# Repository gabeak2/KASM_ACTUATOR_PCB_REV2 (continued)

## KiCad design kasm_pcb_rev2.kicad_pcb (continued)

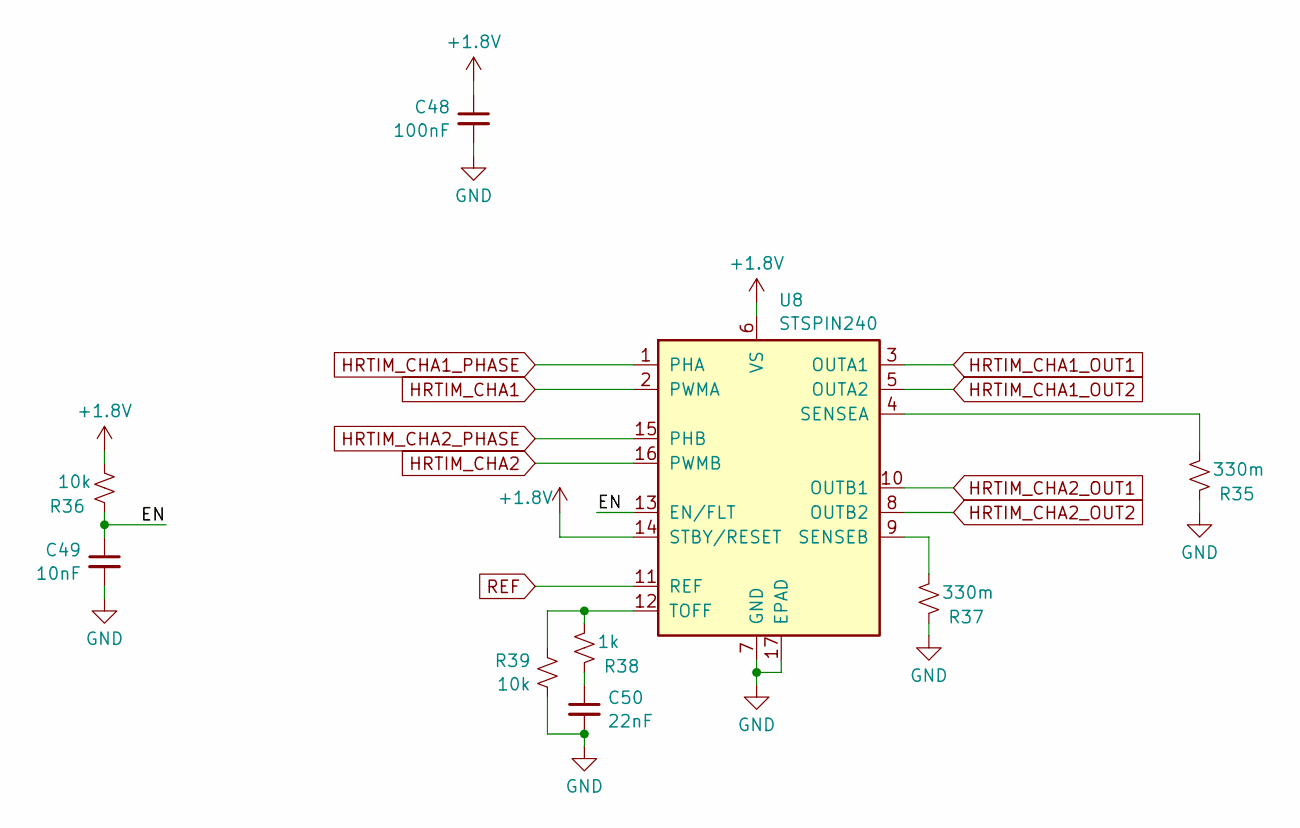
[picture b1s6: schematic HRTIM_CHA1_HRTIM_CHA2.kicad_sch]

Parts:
C48: 100nF; C_0402_1005Metric; LCSC C1525
C49: 10nF; C_0402_1005Metric; LCSC C15195
C50: 22nF; C_0402_1005Metric; LCSC C1532
R35, R37: 330m; R_0402_1005Metric; LCSC C332660
R36, R39: 10k; R_0402_1005Metric; LCSC C25744
R38: 1k; R_0402_1005Metric; LCSC C11702
U8: STSPIN240; VQFN-16-1EP_3x3mm_P0.5mm_EP1.8x1.8mm; LCSC C962258

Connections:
+1.8V: C48.1, R36.1, U8.6 (VS), U8.14 (STBY/RESET); also elsewhere on the board
/Actuators/HRTIM_CHA1_HRTIM_CHA2/EN: C49.1, R36.2, U8.13 (EN/FLT)
GND: C48.2, C49.2, C50.2, R35.2, R37.2, R39.2, U8.7 (GND), U8.17 (EPAD); also elsewhere on the board
HRTIM_CHA1: U8.2 (PWMA); also elsewhere on the board
HRTIM_CHA1_OUT1: U8.3 (OUTA1); also elsewhere on the board
HRTIM_CHA1_OUT2: U8.5 (OUTA2); also elsewhere on the board
HRTIM_CHA1_PHASE: U8.1 (PHA); also elsewhere on the board
HRTIM_CHA2: U8.16 (PWMB); also elsewhere on the board
HRTIM_CHA2_OUT1: U8.10 (OUTB1); also elsewhere on the board
HRTIM_CHA2_OUT2: U8.8 (OUTB2); also elsewhere on the board
HRTIM_CHA2_PHASE: U8.15 (PHB); also elsewhere on the board
unnamed: C50.1, R38.2
unnamed: R35.1, U8.4 (SENSEA)
unnamed: R37.1, U8.9 (SENSEB)
unnamed: R38.1, R39.1, U8.12 (TOFF)
REF: U8.11 (REF); also elsewhere on the board

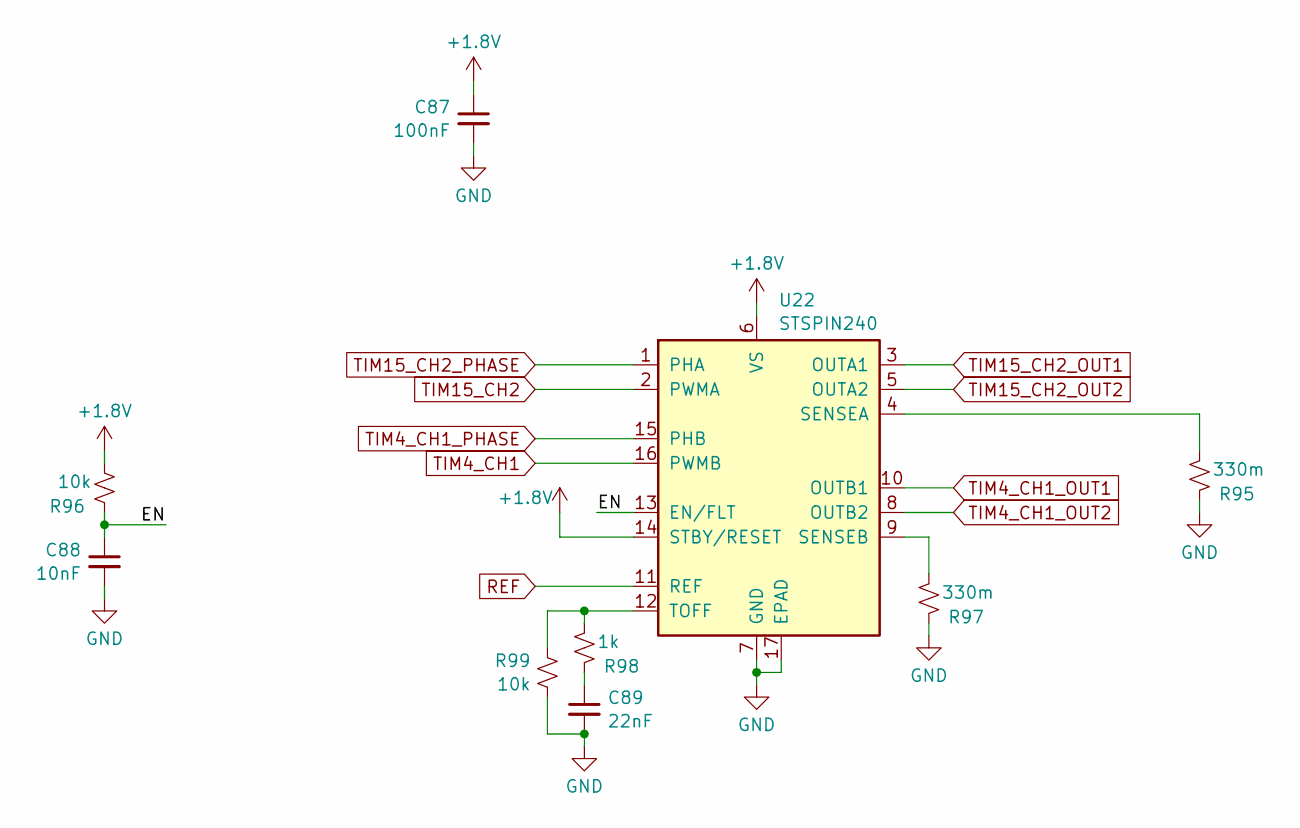
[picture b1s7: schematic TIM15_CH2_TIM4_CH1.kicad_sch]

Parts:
C87: 100nF; C_0402_1005Metric; LCSC C1525
C88: 10nF; C_0402_1005Metric; LCSC C15195
C89: 22nF; C_0402_1005Metric; LCSC C1532
R95, R97: 330m; R_0402_1005Metric; LCSC C332660
R96, R99: 10k; R_0402_1005Metric; LCSC C25744
R98: 1k; R_0402_1005Metric; LCSC C11702
U22: STSPIN240; VQFN-16-1EP_3x3mm_P0.5mm_EP1.8x1.8mm; LCSC C962258

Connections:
+1.8V: C87.1, R96.1, U22.6 (VS), U22.14 (STBY/RESET); also elsewhere on the board
/Actuators/TIM15_CH2_TIM4_CH1/EN: C88.1, R96.2, U22.13 (EN/FLT)
GND: C87.2, C88.2, C89.2, R95.2, R97.2, R99.2, U22.7 (GND), U22.17 (EPAD); also elsewhere on the board
unnamed: C89.1, R98.2
unnamed: R95.1, U22.4 (SENSEA)
unnamed: R97.1, U22.9 (SENSEB)
unnamed: R98.1, R99.1, U22.12 (TOFF)
REF: U22.11 (REF); also elsewhere on the board
TIM4_CH1: U22.16 (PWMB); also elsewhere on the board
TIM4_CH1_OUT1: U22.10 (OUTB1); also elsewhere on the board
TIM4_CH1_OUT2: U22.8 (OUTB2); also elsewhere on the board
TIM4_CH1_PHASE: U22.15 (PHB); also elsewhere on the board
TIM15_CH2: U22.2 (PWMA); also elsewhere on the board
TIM15_CH2_OUT1: U22.3 (OUTA1); also elsewhere on the board
TIM15_CH2_OUT2: U22.5 (OUTA2); also elsewhere on the board
TIM15_CH2_PHASE: U22.1 (PHA); also elsewhere on the board

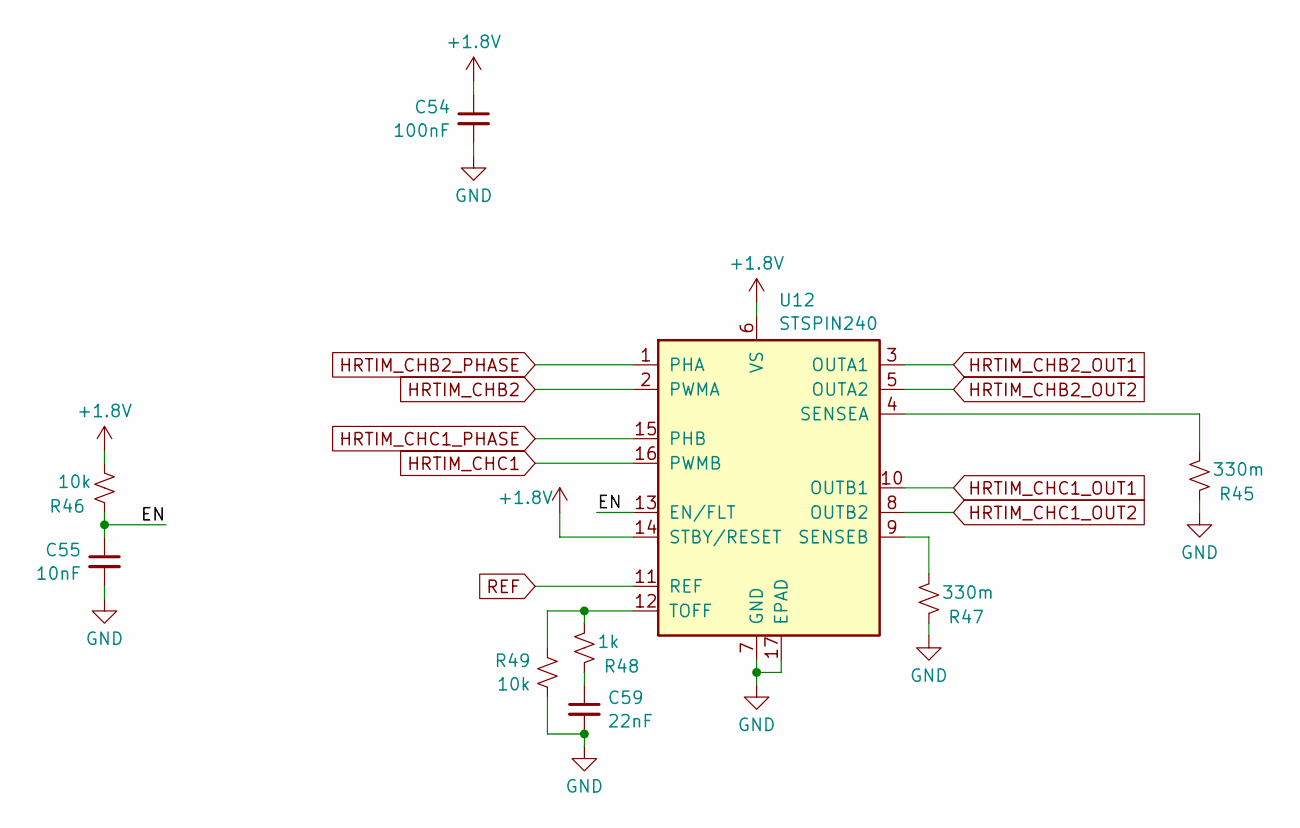
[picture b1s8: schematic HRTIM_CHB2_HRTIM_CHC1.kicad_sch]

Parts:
C54: 100nF; C_0402_1005Metric; LCSC C1525
C55: 10nF; C_0402_1005Metric; LCSC C15195
C59: 22nF; C_0402_1005Metric; LCSC C1532
R45, R47: 330m; R_0402_1005Metric; LCSC C332660
R46, R49: 10k; R_0402_1005Metric; LCSC C25744
R48: 1k; R_0402_1005Metric; LCSC C11702
U12: STSPIN240; VQFN-16-1EP_3x3mm_P0.5mm_EP1.8x1.8mm; LCSC C962258

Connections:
+1.8V: C54.1, R46.1, U12.6 (VS), U12.14 (STBY/RESET); also elsewhere on the board
/Actuators/HRTIM_CHB2_HRTIM_CHC1/EN: C55.1, R46.2, U12.13 (EN/FLT)
GND: C54.2, C55.2, C59.2, R45.2, R47.2, R49.2, U12.7 (GND), U12.17 (EPAD); also elsewhere on the board
HRTIM_CHB2: U12.2 (PWMA); also elsewhere on the board
HRTIM_CHB2_OUT1: U12.3 (OUTA1); also elsewhere on the board
HRTIM_CHB2_OUT2: U12.5 (OUTA2); also elsewhere on the board
HRTIM_CHB2_PHASE: U12.1 (PHA); also elsewhere on the board
HRTIM_CHC1: U12.16 (PWMB); also elsewhere on the board
HRTIM_CHC1_OUT1: U12.10 (OUTB1); also elsewhere on the board
HRTIM_CHC1_OUT2: U12.8 (OUTB2); also elsewhere on the board
HRTIM_CHC1_PHASE: U12.15 (PHB); also elsewhere on the board
unnamed: C59.1, R48.2
unnamed: R45.1, U12.4 (SENSEA)
unnamed: R47.1, U12.9 (SENSEB)
unnamed: R48.1, R49.1, U12.12 (TOFF)
REF: U12.11 (REF); also elsewhere on the board

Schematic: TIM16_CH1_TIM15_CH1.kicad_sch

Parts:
C78: 100nF; C_0402_1005Metric; LCSC C1525
C79: 10nF; C_0402_1005Metric; LCSC C15195
C80: 22nF; C_0402_1005Metric; LCSC C1532
R80, R82: 330m; R_0402_1005Metric; LCSC C332660
R81, R84: 10k; R_0402_1005Metric; LCSC C25744
R83: 1k; R_0402_1005Metric; LCSC C11702
U19: STSPIN240; VQFN-16-1EP_3x3mm_P0.5mm_EP1.8x1.8mm; LCSC C962258

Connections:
+1.8V: C78.1, R81.1, U19.6 (VS), U19.14 (STBY/RESET); also elsewhere on the board
/Actuators/TIM16_CH1_TIM15_CH1/EN: C79.1, R81.2, U19.13 (EN/FLT)
GND: C78.2, C79.2, C80.2, R80.2, R82.2, R84.2, U19.7 (GND), U19.17 (EPAD); also elsewhere on the board
unnamed: C80.1, R83.2
unnamed: R80.1, U19.4 (SENSEA)
unnamed: R82.1, U19.9 (SENSEB)
unnamed: R83.1, R84.1, U19.12 (TOFF)
REF: U19.11 (REF); also elsewhere on the board
TIM15_CH1: U19.16 (PWMB); also elsewhere on the board
TIM15_CH1_OUT1: U19.10 (OUTB1); also elsewhere on the board
TIM15_CH1_OUT2: U19.8 (OUTB2); also elsewhere on the board
TIM15_CH1_PHASE: U19.15 (PHB); also elsewhere on the board
TIM16_CH1: U19.2 (PWMA); also elsewhere on the board
TIM16_CH1_OUT1: U19.3 (OUTA1); also elsewhere on the board
TIM16_CH1_OUT2: U19.5 (OUTA2); also elsewhere on the board
TIM16_CH1_PHASE: U19.1 (PHA); also elsewhere on the board

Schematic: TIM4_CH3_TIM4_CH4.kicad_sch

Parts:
C75: 100nF; C_0402_1005Metric; LCSC C1525
C76: 10nF; C_0402_1005Metric; LCSC C15195
C77: 22nF; C_0402_1005Metric; LCSC C1532
R75, R77: 330m; R_0402_1005Metric; LCSC C332660
R76, R79: 10k; R_0402_1005Metric; LCSC C25744
R78: 1k; R_0402_1005Metric; LCSC C11702
U18: STSPIN240; VQFN-16-1EP_3x3mm_P0.5mm_EP1.8x1.8mm; LCSC C962258

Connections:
+1.8V: C75.1, R76.1, U18.6 (VS), U18.14 (STBY/RESET); also elsewhere on the board
/Actuators/TIM4_CH3_TIM4_CH4/EN: C76.1, R76.2, U18.13 (EN/FLT)
GND: C75.2, C76.2, C77.2, R75.2, R77.2, R79.2, U18.7 (GND), U18.17 (EPAD); also elsewhere on the board
unnamed: C77.1, R78.2
unnamed: R75.1, U18.4 (SENSEA)
unnamed: R77.1, U18.9 (SENSEB)
unnamed: R78.1, R79.1, U18.12 (TOFF)
REF: U18.11 (REF); also elsewhere on the board
TIM4_CH3: U18.2 (PWMA); also elsewhere on the board
TIM4_CH3_OUT1: U18.3 (OUTA1); also elsewhere on the board
TIM4_CH3_OUT2: U18.5 (OUTA2); also elsewhere on the board
TIM4_CH3_PHASE: U18.1 (PHA); also elsewhere on the board
TIM4_CH4: U18.16 (PWMB); also elsewhere on the board
TIM4_CH4_OUT1: U18.10 (OUTB1); also elsewhere on the board
TIM4_CH4_OUT2: U18.8 (OUTB2); also elsewhere on the board
TIM4_CH4_PHASE: U18.15 (PHB); also elsewhere on the board

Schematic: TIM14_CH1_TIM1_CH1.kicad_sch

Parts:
C84: 100nF; C_0402_1005Metric; LCSC C1525
C85: 10nF; C_0402_1005Metric; LCSC C15195
C86: 22nF; C_0402_1005Metric; LCSC C1532
R90, R92: 330m; R_0402_1005Metric; LCSC C332660
R91, R94: 10k; R_0402_1005Metric; LCSC C25744
R93: 1k; R_0402_1005Metric; LCSC C11702
U21: STSPIN240; VQFN-16-1EP_3x3mm_P0.5mm_EP1.8x1.8mm; LCSC C962258

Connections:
+1.8V: C84.1, R91.1, U21.6 (VS), U21.14 (STBY/RESET); also elsewhere on the board
/Actuators/TIM14_CH1_TIM1_CH1/EN: C85.1, R91.2, U21.13 (EN/FLT)
GND: C84.2, C85.2, C86.2, R90.2, R92.2, R94.2, U21.7 (GND), U21.17 (EPAD); also elsewhere on the board
unnamed: C86.1, R93.2
unnamed: R90.1, U21.4 (SENSEA)
unnamed: R92.1, U21.9 (SENSEB)
unnamed: R93.1, R94.1, U21.12 (TOFF)
REF: U21.11 (REF); also elsewhere on the board
TIM1_CH1: U21.16 (PWMB); also elsewhere on the board
TIM1_CH1_OUT1: U21.10 (OUTB1); also elsewhere on the board
TIM1_CH1_OUT2: U21.8 (OUTB2); also elsewhere on the board
TIM1_CH1_PHASE: U21.15 (PHB); also elsewhere on the board
TIM14_CH1: U21.2 (PWMA); also elsewhere on the board
TIM14_CH1_OUT1: U21.3 (OUTA1); also elsewhere on the board
TIM14_CH1_OUT2: U21.5 (OUTA2); also elsewhere on the board
TIM14_CH1_PHASE: U21.1 (PHA); also elsewhere on the board

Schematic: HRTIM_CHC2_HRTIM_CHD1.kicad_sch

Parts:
C60: 100nF; C_0402_1005Metric; LCSC C1525
C61: 10nF; C_0402_1005Metric; LCSC C15195
C62: 22nF; C_0402_1005Metric; LCSC C1532
R50, R52: 330m; R_0402_1005Metric; LCSC C332660
R51, R54: 10k; R_0402_1005Metric; LCSC C25744
R53: 1k; R_0402_1005Metric; LCSC C11702
TP28: "HRTCHC2_P"; TestPoint_Pad_1.0x1.0mm
TP29: "HRTCHC2"; TestPoint_Pad_1.0x1.0mm
TP30: "HRTCHC2_O1"; TestPoint_Pad_1.0x1.0mm
TP31: "HRTCHC2_O2"; TestPoint_Pad_1.0x1.0mm
TP32: "HRTCHD1_P"; TestPoint_Pad_1.0x1.0mm
TP33: "HRTCHD1"; TestPoint_Pad_1.0x1.0mm
TP34: "HRTCHD1_O1"; TestPoint_Pad_1.0x1.0mm
TP35: "HRTCHD1_O2"; TestPoint_Pad_1.0x1.0mm
U13: STSPIN240; VQFN-16-1EP_3x3mm_P0.5mm_EP1.8x1.8mm; LCSC C962258

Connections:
+1.8V: C60.1, R51.1, U13.6 (VS), U13.14 (STBY/RESET); also elsewhere on the board
EN_U13: C61.1, R51.2, U13.13 (EN/FLT); also elsewhere on the board
GND: C60.2, C61.2, C62.2, R50.2, R52.2, R54.2, U13.7 (GND), U13.17 (EPAD); also elsewhere on the board
HRTIM_CHC2: TP29.1, U13.2 (PWMA); also elsewhere on the board
HRTIM_CHC2_OUT1: TP30.1, U13.3 (OUTA1); also elsewhere on the board
HRTIM_CHC2_OUT2: TP31.1, U13.5 (OUTA2); also elsewhere on the board
HRTIM_CHC2_PHASE: TP28.1, U13.1 (PHA); also elsewhere on the board
HRTIM_CHD1: TP33.1, U13.16 (PWMB); also elsewhere on the board
HRTIM_CHD1_OUT1: TP34.1, U13.10 (OUTB1); also elsewhere on the board
HRTIM_CHD1_OUT2: TP35.1, U13.8 (OUTB2); also elsewhere on the board
HRTIM_CHD1_PHASE: TP32.1, U13.15 (PHB); also elsewhere on the board
unnamed: C62.1, R53.2
unnamed: R50.1, U13.4 (SENSEA)
unnamed: R52.1, U13.9 (SENSEB)
unnamed: R53.1, R54.1, U13.12 (TOFF)
REF: U13.11 (REF); also elsewhere on the board

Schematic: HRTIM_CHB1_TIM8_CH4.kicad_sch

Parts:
C51: 100nF; C_0402_1005Metric; LCSC C1525
C52: 10nF; C_0402_1005Metric; LCSC C15195
C53: 22nF; C_0402_1005Metric; LCSC C1532
R40, R42: 330m; R_0402_1005Metric; LCSC C332660
R41, R44: 10k; R_0402_1005Metric; LCSC C25744
R43: 1k; R_0402_1005Metric; LCSC C11702
U11: STSPIN240; VQFN-16-1EP_3x3mm_P0.5mm_EP1.8x1.8mm; LCSC C962258

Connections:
+1.8V: C51.1, R41.1, U11.6 (VS), U11.14 (STBY/RESET); also elsewhere on the board
/Actuators/HRTIM_CHB1_TIM8_CH4/EN: C52.1, R41.2, U11.13 (EN/FLT)
GND: C51.2, C52.2, C53.2, R40.2, R42.2, R44.2, U11.7 (GND), U11.17 (EPAD); also elsewhere on the board
HRTIM_CHB1: U11.2 (PWMA); also elsewhere on the board
HRTIM_CHB1_OUT1: U11.3 (OUTA1); also elsewhere on the board
HRTIM_CHB1_OUT2: U11.5 (OUTA2); also elsewhere on the board
HRTIM_CHB1_PHASE: U11.1 (PHA); also elsewhere on the board
unnamed: C53.1, R43.2
unnamed: R40.1, U11.4 (SENSEA)
unnamed: R42.1, U11.9 (SENSEB)
unnamed: R43.1, R44.1, U11.12 (TOFF)
REF: U11.11 (REF); also elsewhere on the board
TIM8_CH4: U11.16 (PWMB); also elsewhere on the board
TIM8_CH4_OUT1: U11.10 (OUTB1); also elsewhere on the board
TIM8_CH4_OUT2: U11.8 (OUTB2); also elsewhere on the board
TIM8_CH4_PHASE: U11.15 (PHB); also elsewhere on the board

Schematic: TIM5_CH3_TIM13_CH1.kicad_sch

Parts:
C81: 100nF; C_0402_1005Metric; LCSC C1525
C82: 10nF; C_0402_1005Metric; LCSC C15195
C83: 22nF; C_0402_1005Metric; LCSC C1532
R85, R87: 330m; R_0402_1005Metric; LCSC C332660
R86, R89: 10k; R_0402_1005Metric; LCSC C25744
R88: 1k; R_0402_1005Metric; LCSC C11702
U20: STSPIN240; VQFN-16-1EP_3x3mm_P0.5mm_EP1.8x1.8mm; LCSC C962258

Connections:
+1.8V: C81.1, R86.1, U20.6 (VS), U20.14 (STBY/RESET); also elsewhere on the board
/Actuators/TIM5_CH3_TIM13_CH1/EN: C82.1, R86.2, U20.13 (EN/FLT)
GND: C81.2, C82.2, C83.2, R85.2, R87.2, R89.2, U20.7 (GND), U20.17 (EPAD); also elsewhere on the board
unnamed: C83.1, R88.2
unnamed: R85.1, U20.4 (SENSEA)
unnamed: R87.1, U20.9 (SENSEB)
unnamed: R88.1, R89.1, U20.12 (TOFF)
REF: U20.11 (REF); also elsewhere on the board
TIM5_CH3: U20.2 (PWMA); also elsewhere on the board
TIM5_CH3_OUT1: U20.3 (OUTA1); also elsewhere on the board
TIM5_CH3_OUT2: U20.5 (OUTA2); also elsewhere on the board
TIM5_CH3_PHASE: U20.1 (PHA); also elsewhere on the board
TIM13_CH1: U20.16 (PWMB); also elsewhere on the board
TIM13_CH1_OUT1: U20.10 (OUTB1); also elsewhere on the board
TIM13_CH1_OUT2: U20.8 (OUTB2); also elsewhere on the board
TIM13_CH1_PHASE: U20.15 (PHB); also elsewhere on the board

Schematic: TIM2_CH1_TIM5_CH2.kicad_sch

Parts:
C72: 100nF; C_0402_1005Metric; LCSC C1525
C73: 10nF; C_0402_1005Metric; LCSC C15195
C74: 22nF; C_0402_1005Metric; LCSC C1532
R70, R72: 330m; R_0402_1005Metric; LCSC C332660
R71, R74: 10k; R_0402_1005Metric; LCSC C25744
R73: 1k; R_0402_1005Metric; LCSC C11702
U17: STSPIN240; VQFN-16-1EP_3x3mm_P0.5mm_EP1.8x1.8mm; LCSC C962258

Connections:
+1.8V: C72.1, R71.1, U17.6 (VS), U17.14 (STBY/RESET); also elsewhere on the board
/Actuators/TIM2_CH1_TIM5_CH2/EN: C73.1, R71.2, U17.13 (EN/FLT)
GND: C72.2, C73.2, C74.2, R70.2, R72.2, R74.2, U17.7 (GND), U17.17 (EPAD); also elsewhere on the board
unnamed: C74.1, R73.2
unnamed: R70.1, U17.4 (SENSEA)
unnamed: R72.1, U17.9 (SENSEB)
unnamed: R73.1, R74.1, U17.12 (TOFF)
REF: U17.11 (REF); also elsewhere on the board
TIM2_CH1: U17.2 (PWMA); also elsewhere on the board
TIM2_CH1_OUT1: U17.3 (OUTA1); also elsewhere on the board
TIM2_CH1_OUT2: U17.5 (OUTA2); also elsewhere on the board
TIM2_CH1_PHASE: U17.1 (PHA); also elsewhere on the board
TIM5_CH2: U17.16 (PWMB); also elsewhere on the board
TIM5_CH2_OUT1: U17.10 (OUTB1); also elsewhere on the board
TIM5_CH2_OUT2: U17.8 (OUTB2); also elsewhere on the board
TIM5_CH2_PHASE: U17.15 (PHB); also elsewhere on the board

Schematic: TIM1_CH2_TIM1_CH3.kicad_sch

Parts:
C66: 100nF; C_0402_1005Metric; LCSC C1525
C67: 10nF; C_0402_1005Metric; LCSC C15195
C68: 22nF; C_0402_1005Metric; LCSC C1532
R60, R62: 330m; R_0402_1005Metric; LCSC C332660
R61, R64: 10k; R_0402_1005Metric; LCSC C25744
R63: 1k; R_0402_1005Metric; LCSC C11702
U15: STSPIN240; VQFN-16-1EP_3x3mm_P0.5mm_EP1.8x1.8mm; LCSC C962258

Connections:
+1.8V: C66.1, R61.1, U15.6 (VS), U15.14 (STBY/RESET); also elsewhere on the board
/Actuators/TIM1_CH2_TIM1_CH3/EN: C67.1, R61.2, U15.13 (EN/FLT)
GND: C66.2, C67.2, C68.2, R60.2, R62.2, R64.2, U15.7 (GND), U15.17 (EPAD); also elsewhere on the board
unnamed: C68.1, R63.2
unnamed: R60.1, U15.4 (SENSEA)
unnamed: R62.1, U15.9 (SENSEB)
unnamed: R63.1, R64.1, U15.12 (TOFF)
REF: U15.11 (REF); also elsewhere on the board
TIM1_CH2: U15.2 (PWMA); also elsewhere on the board
TIM1_CH2_OUT1: U15.3 (OUTA1); also elsewhere on the board
TIM1_CH2_OUT2: U15.5 (OUTA2); also elsewhere on the board
TIM1_CH2_PHASE: U15.1 (PHA); also elsewhere on the board
TIM1_CH3: U15.16 (PWMB); also elsewhere on the board
TIM1_CH3_OUT1: U15.10 (OUTB1); also elsewhere on the board
TIM1_CH3_OUT2: U15.8 (OUTB2); also elsewhere on the board
TIM1_CH3_PHASE: U15.15 (PHB); also elsewhere on the board

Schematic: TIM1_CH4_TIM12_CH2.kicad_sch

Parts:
C69: 100nF; C_0402_1005Metric; LCSC C1525
C70: 10nF; C_0402_1005Metric; LCSC C15195
C71: 22nF; C_0402_1005Metric; LCSC C1532
R65, R67: 330m; R_0402_1005Metric; LCSC C332660
R66, R69: 10k; R_0402_1005Metric; LCSC C25744
R68: 1k; R_0402_1005Metric; LCSC C11702
TP18: "T1CH4_P"; TestPoint_Pad_1.0x1.0mm
TP19: "T1CH4"; TestPoint_Pad_1.0x1.0mm
TP20: "T1CH4_O1"; TestPoint_Pad_1.0x1.0mm
TP21: "T1CH4_O2"; TestPoint_Pad_1.0x1.0mm
TP22: "T12CH2_P"; TestPoint_Pad_1.0x1.0mm
TP23: "T12CH2"; TestPoint_Pad_1.0x1.0mm
TP24: "T12CH2_O1"; TestPoint_Pad_1.0x1.0mm
TP25: "T12CH2_O2"; TestPoint_Pad_1.0x1.0mm
U16: STSPIN240; VQFN-16-1EP_3x3mm_P0.5mm_EP1.8x1.8mm; LCSC C962258

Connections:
+1.8V: C69.1, R66.1, U16.6 (VS), U16.14 (STBY/RESET); also elsewhere on the board
EN_U16: C70.1, R66.2, U16.13 (EN/FLT); also elsewhere on the board
GND: C69.2, C70.2, C71.2, R65.2, R67.2, R69.2, U16.7 (GND), U16.17 (EPAD); also elsewhere on the board
unnamed: C71.1, R68.2
unnamed: R65.1, U16.4 (SENSEA)
unnamed: R67.1, U16.9 (SENSEB)
unnamed: R68.1, R69.1, U16.12 (TOFF)
REF: U16.11 (REF); also elsewhere on the board
TIM1_CH4: TP19.1, U16.2 (PWMA); also elsewhere on the board
TIM1_CH4_OUT1: TP20.1, U16.3 (OUTA1); also elsewhere on the board
TIM1_CH4_OUT2: TP21.1, U16.5 (OUTA2); also elsewhere on the board
TIM1_CH4_PHASE: TP18.1, U16.1 (PHA); also elsewhere on the board
TIM12_CH2: TP23.1, U16.16 (PWMB); also elsewhere on the board
TIM12_CH2_OUT1: TP24.1, U16.10 (OUTB1); also elsewhere on the board
TIM12_CH2_OUT2: TP25.1, U16.8 (OUTB2); also elsewhere on the board
TIM12_CH2_PHASE: TP22.1, U16.15 (PHB); also elsewhere on the board

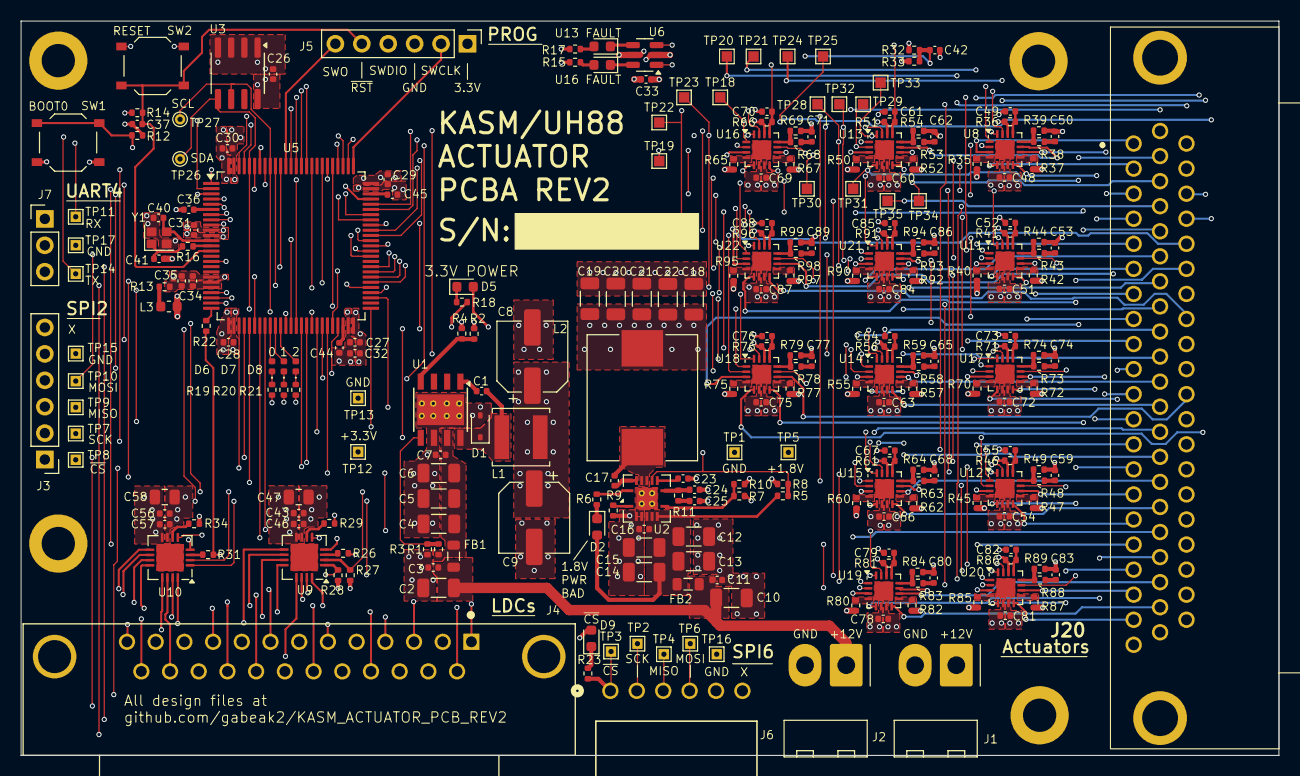
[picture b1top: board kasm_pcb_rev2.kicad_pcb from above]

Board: 6 copper layers, 121.0 x 70.6 mm, 267 parts (0 on the bottom side), 251 nets.

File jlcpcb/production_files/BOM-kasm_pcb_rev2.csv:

Comment,Designator,Footprint,LCSC
FerriteBead_Small,"FB1,FB2",L_0805_2012Metric,C1017
150pF,C24,C_0402_1005Metric,C106998
12.4k,R7,R_0402_1005Metric,C11692
1k,"R15,R17,R38,R43,R48,R53,R58,R63,R68,R73,R78,R83,R88,R93,R98",R_0402_1005Metric,C11702
2.2uF,"C44,C45",C_0402_1005Metric,C12530
442,R16,R_0402_1005Metric,C126137
3.01k,R11,R_0402_1005Metric,C137994
240k,R9,R_0402_1005Metric,C138030
18k,"R3,R8",R_0402_1005Metric,C138044
49.9,R22,R_0402_1005Metric,C144754
100uF,"C18,C19,C20,C21,C22",C_1206_3216Metric,C15008
10nF,"C49,C52,C55,C61,C64,C67,C70,C73,C76,C79,C82,C85,C88",C_0402_1005Metric,C15195
100nF,"C11,C16,C17,C26,C27,C28,C29,C3,C30,C31,C33,C34,C36,C37,C48,C51,C54,C60,C63,C66,C69,C7,C72,C75,C78,C81,C84,C87",C_0402_1005Metric,C1525
2.2nF,C23,C_0402_1005Metric,C1531
22nF,"C50,C53,C59,C62,C65,C68,C71,C74,C77,C80,C83,C86,C89",C_0402_1005Metric,C1532
15pF,"C40,C41",C_0402_1005Metric,C1548
6.8uH,L2,L_Chilisin_BMRF00101040,C167231
56uH,L1,L_Changjiang_FNR5020S,C167944
0,"R26,R31",R_0402_1005Metric,C17168
D_Schottky,D1,D_SOD-323,C191023
LED_WHITE,"D6,D7,D8",LED_0402_1005Metric,C20613596
LED,"D2,D3,D4",LED_0603_1608Metric,C2286
4.7uF,"C32,C35,C43,C56",C_0402_1005Metric,C23733
220,"R19,R20,R21,R23,R33",R_0402_1005Metric,C25091
100k,"R1,R5",R_0402_1005Metric,C25741
10k,"R10,R12,R2,R36,R39,R41,R44,R46,R49,R51,R54,R56,R59,R61,R64,R66,R69,R71,R74,R76,R79,R81,R84,R86,R89,R91,R94,R96,R99",R_0402_1005Metric,C25744
11k,R14,R_0402_1005Metric,C25749
2.2k,R32,R_0402_1005Metric,C25879
4.7k,"R27,R28,R29,R34,R6",R_0402_1005Metric,C25900
5.9k,R4,R_0402_1005Metric,C270591
"24MHz, 9pF",Y1,Crystal_SMD_SeikoEpson_FA128-4Pin_2.0x1.6mm,C2929399
TPS54620,U2,Texas_S-PVQFN-N14_ThermalVias,C29438
100nF,"C46,C57",C_0402_1005Metric,C307331
SW_Push,"SW1,SW2",SW_Push_1P1T_XKB_TS-1187A,C318884
330m,"R35,R37,R40,R42,R45,R47,R50,R52,R55,R57,R60,R62,R65,R67,R70,R72,R75,R77,R80,R82,R85,R87,R90,R92,R95,R97",R_0402_1005Metric,C332660
74LVC2G07,U6,SOT-23-6,C37708
STM32H750VBTx,U5,LQFP-100_14x14mm_P0.5mm,C404010
10,R13,R_0402_1005Metric,C409845
10uF,"C47,C58",C_0805_2012Metric,C440198
10uF,"C10,C12,C13,C14,C15,C2,C4,C5,C6",C_1206_3216Metric,C454102
100uH,L3,L_0603_1608Metric,C51942
82nF,C25,C_0402_1005Metric,C524617
1uF,C42,C_0402_1005Metric,C52923
220uF,"C8,C9",CP_Elec_6.3x5.4,C59953
10nF,C1,C_0402_1005Metric,C60133
M24C02-WMN,U3,SOIC-8_3.9x4.9mm_P1.27mm,C7562
STSPIN240,"U11,U12,U13,U14,U15,U16,U17,U18,U19,U20,U21,U22,U8",VQFN-16-1EP_3x3mm_P0.5mm_EP1.8x1.8mm,C962258
LED_GREEN,"D5,D9",LED_0603_1608Metric,C965804
LDC1614,"U10,U9",WQFN-16-1EP_4x4mm_P0.5mm_EP2.6x2.6mm,C968448
TPS5430DDA,U1,TI_SO-PowerPAD-8_ThermalVias,C9864
100,R18,R_0402_1005Metric,C106232
DB25_Receptacle_MountingHoles,J4,TE_5747846-4,
"""HRTCHD1""",TP33,TestPoint_Pad_1.0x1.0mm,
"""T12CH2_P""",TP22,TestPoint_Pad_1.0x1.0mm,
"""GND""",TP13,TestPoint_THTPad_1.0x1.0mm_Drill0.5mm,
Conn_01x02,J1,Molex_KK-396_A-41792-0002_1x02_P3.96mm_Horizontal,
"""GND""",TP15,TestPoint_THTPad_1.0x1.0mm_Drill0.5mm,
MountingHole_Pad,H3,MountingHole_3.2mm_M3_DIN965_Pad,
"""HRTCHC2_O2""",TP31,TestPoint_Pad_1.0x1.0mm,
"""HRTCHC2""",TP29,TestPoint_Pad_1.0x1.0mm,
"""GND""",TP16,TestPoint_THTPad_1.0x1.0mm_Drill0.5mm,
Conn_01x06,J6,CONN_A-7478-06A_MOL,
"""TX4""",TP14,TestPoint_THTPad_1.0x1.0mm_Drill0.5mm,
"""1.8V""",TP5,TestPoint_THTPad_1.0x1.0mm_Drill0.5mm,
"""T12CH2""",TP23,TestPoint_Pad_1.0x1.0mm,
"""T12CH2_O1""",TP24,TestPoint_Pad_1.0x1.0mm,
"""GND""",TP1,TestPoint_THTPad_1.0x1.0mm_Drill0.5mm,
"""HRTCHD1_P""",TP32,TestPoint_Pad_1.0x1.0mm,
9564527612,J20,9564527612,
"""HRTCHD1_O1""",TP34,TestPoint_Pad_1.0x1.0mm,
"""T1CH4""",TP19,TestPoint_Pad_1.0x1.0mm,
"""SCK2""",TP7,TestPoint_THTPad_1.0x1.0mm_Drill0.5mm,
"""HRTCHC2_P""",TP28,TestPoint_Pad_1.0x1.0mm,
MountingHole_Pad,H2,MountingHole_3.2mm_M3_DIN965_Pad,
"""MOSI2""",TP10,TestPoint_THTPad_1.0x1.0mm_Drill0.5mm,
"""~{CS2}""",TP8,TestPoint_THTPad_1.0x1.0mm_Drill0.5mm,
"""MISO2""",TP9,TestPoint_THTPad_1.0x1.0mm_Drill0.5mm,
MountingHole_Pad,H1,MountingHole_3.2mm_M3_DIN965_Pad,
"""T12CH2_O2""",TP25,TestPoint_Pad_1.0x1.0mm,
"""MOSI6""",TP6,TestPoint_THTPad_1.0x1.0mm_Drill0.5mm,
MountingHole_Pad,H4,MountingHole_3.2mm_M3_DIN965_Pad,
"""SCL""",TP27,TestPoint_THTPad_D1.0mm_Drill0.5mm,
"""HRTCHC2_O1""",TP30,TestPoint_Pad_1.0x1.0mm,
"""SCK6""",TP2,TestPoint_THTPad_1.0x1.0mm_Drill0.5mm,
Conn_01x06,J5,PinHeader_1x06_P2.54mm_Vertical,
"""T1CH4_O1""",TP20,TestPoint_Pad_1.0x1.0mm,
Conn_01x03,J7,PinHeader_1x03_P2.54mm_Vertical,
Conn_01x06,J3,PinHeader_1x06_P2.54mm_Vertical,
"""HRTCHD1_O2""",TP35,TestPoint_Pad_1.0x1.0mm,
"""T1CH4_O2""",TP21,TestPoint_Pad_1.0x1.0mm,
"""SDA""",TP26,TestPoint_THTPad_D1.0mm_Drill0.5mm,
"""GND""",TP17,TestPoint_THTPad_1.0x1.0mm_Drill0.5mm,
"""RX4""",TP11,TestPoint_THTPad_1.0x1.0mm_Drill0.5mm,
"""3.3V""",TP12,TestPoint_THTPad_1.0x1.0mm_Drill0.5mm,
"""MISO6""",TP4,TestPoint_THTPad_1.0x1.0mm_Drill0.5mm,
"""T1CH4_P""",TP18,TestPoint_Pad_1.0x1.0mm,
"""~{CS6}""",TP3,TestPoint_THTPad_1.0x1.0mm_Drill0.5mm,
Conn_01x02,J2,Molex_KK-396_A-41792-0002_1x02_P3.96mm_Horizontal,
